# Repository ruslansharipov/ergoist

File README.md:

# Ergoist
Ergonomic fully split wireless keyboard

Main features: 
- ortholinear layout with 42 keys including 3 keys thumb cluster (just like on corne)
- all keys are 1u to make it easier to find keycaps
- pcb has big cutaway for battery, that can fit 35x30 lipo battery (should fit lipo 503035 500mA)
- designed to be used with Seeduino Xiao
- wireless only. Wired version will be supported it in future
- no screen integration (yet?)
- power switch (longer battery life, no accidental presses during transportation)
- works with ZMK, latest config can be found [here](https://github.com/ruslansharipov/ergoist-zmk-config)
- reversible PCB makes it cheaper in production (usually you can't order less than 5 pieces, so having 5 of those will make you able to assemble 2.5 keyboards)

Status:
- ~~pcb v0.1 in production~~ received, assembled, tested
- case **re**design

Latest images:

TODO
- update case design
- pcb cleanup
- partlist
- wired version
- screen integration
- touch sensor integration

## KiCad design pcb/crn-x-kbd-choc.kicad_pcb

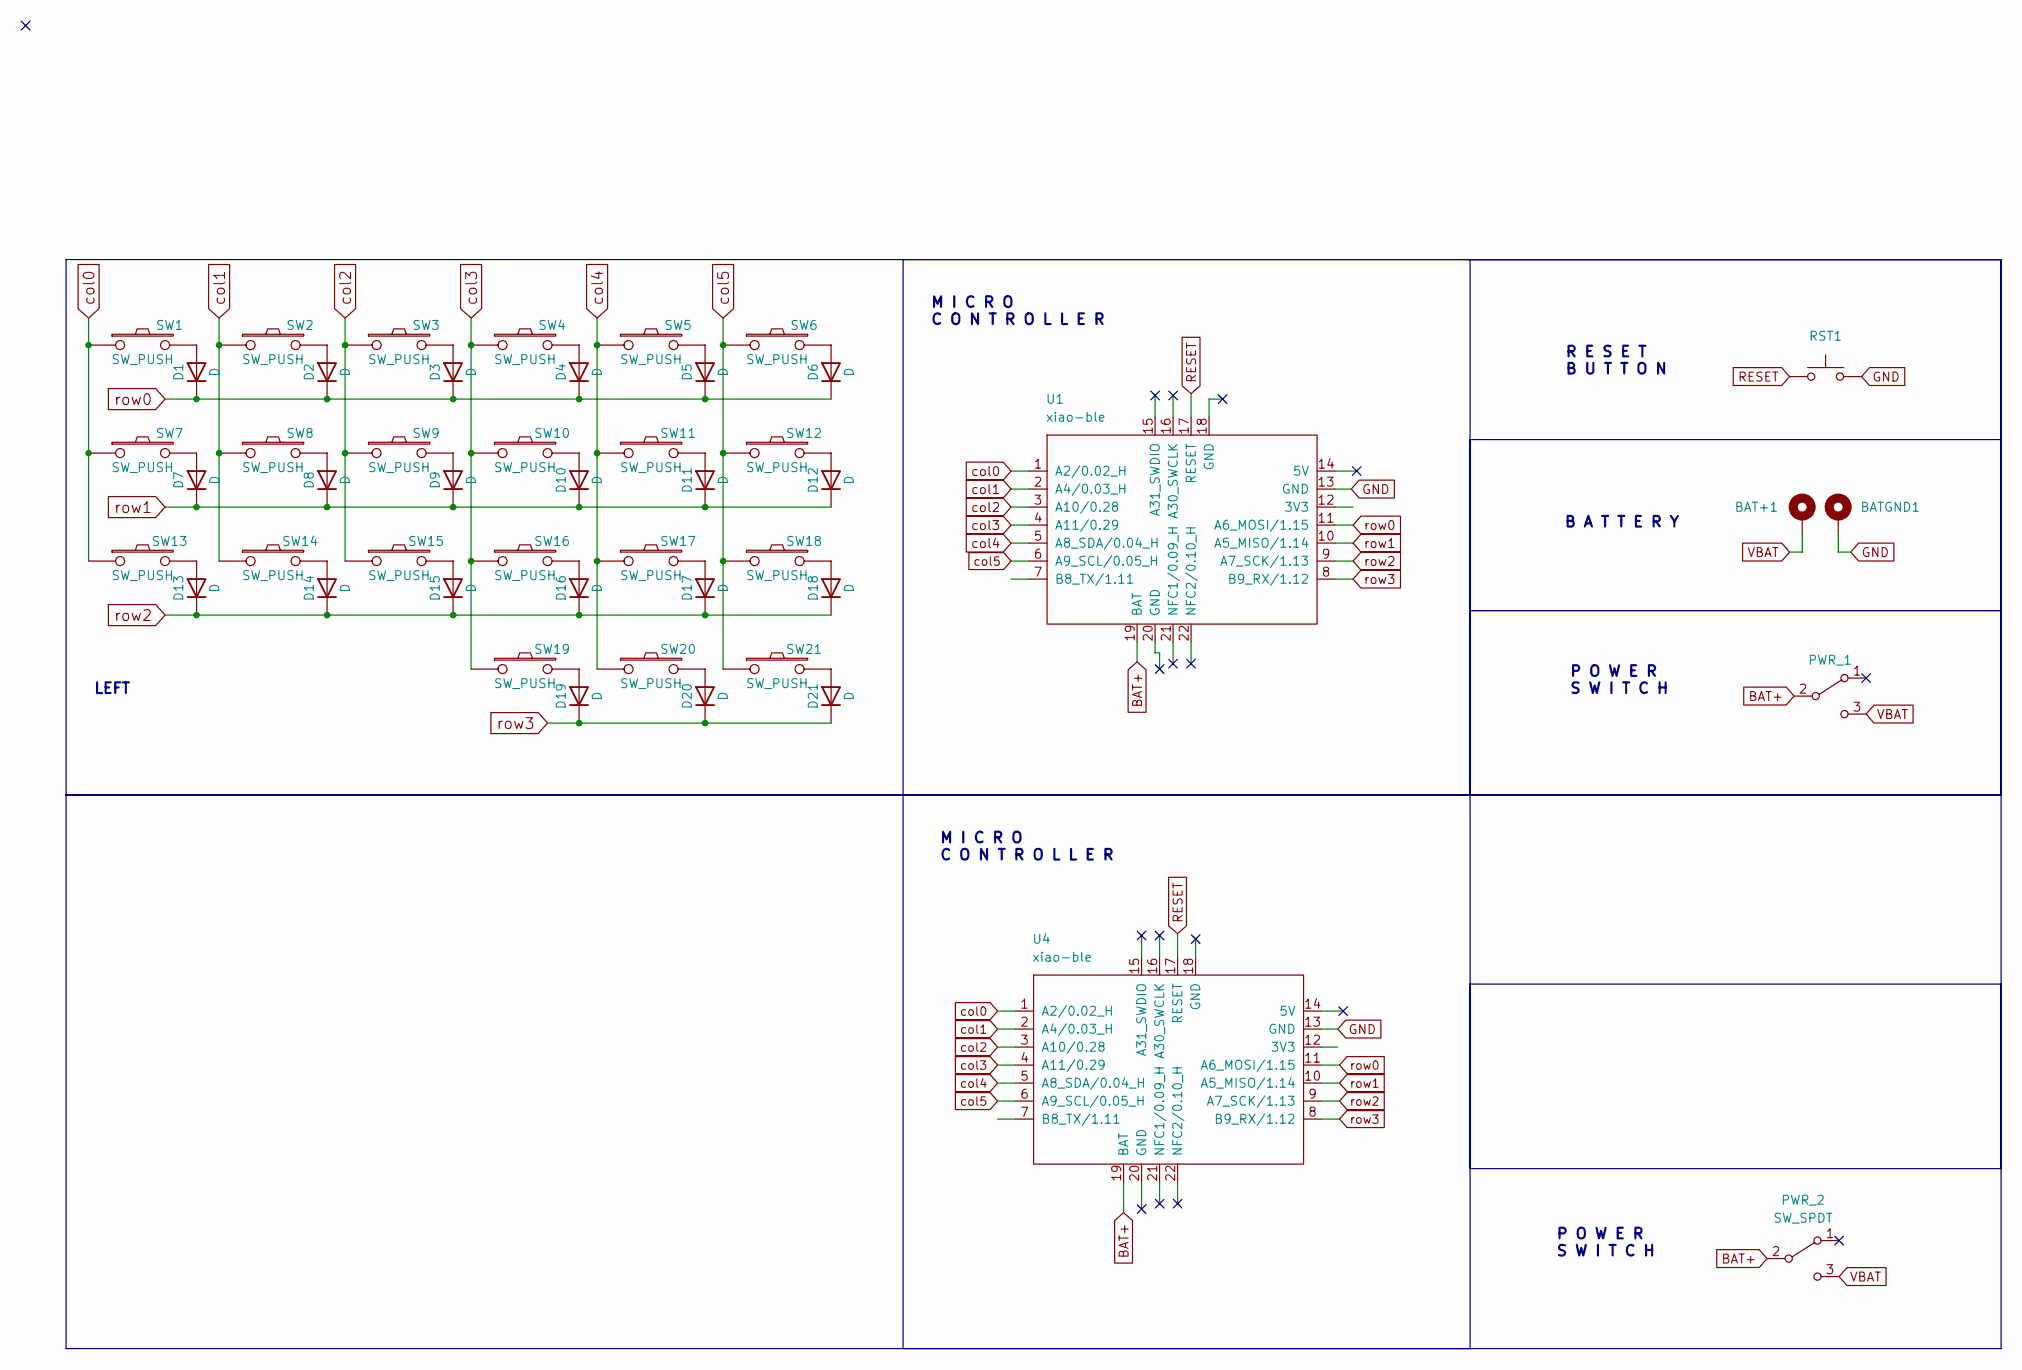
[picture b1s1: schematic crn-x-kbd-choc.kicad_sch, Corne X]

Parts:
BAT+1: +; BatteryPad
BATGND1: -; BatteryPad
D1, D2, D3, D4, D5, D6, D7, D8, D9, D10, D11, D12, D13, D14, D15, D16, D17, D18, D19, D20, D21: D; D3_TH_reversible
PWR_1, PWR_2: SW_SPDT; MSK12C02
RST1: SW_Push; SKHLLCA010_reversible
SW1, SW2, SW3, SW4, SW5, SW6, SW7, SW8, SW9, SW10, SW11, SW12, SW13, SW14, SW15, SW16, SW17, SW18, SW19, SW20, SW21: SW_PUSH; keyswitch_chock12_hotswap_1u_reversible
U1, U4: xiao-ble; xiao-ble-smd-cutout-one-side

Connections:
BAT+: PWR_1.2 (B), PWR_2.2 (B), U1.19 (BAT), U4.19 (BAT)
GND: BATGND1.1, RST1.2, U1.13 (GND), U4.13 (GND)
unnamed: D1.2 (A), SW1.2
unnamed: D2.2 (A), SW2.2
unnamed: D3.2 (A), SW3.2
unnamed: D4.2 (A), SW4.2
unnamed: D5.2 (A), SW5.2
unnamed: D6.2 (A), SW6.2
unnamed: D7.2 (A), SW7.2
unnamed: D8.2 (A), SW8.2
unnamed: D9.2 (A), SW9.2
unnamed: D10.2 (A), SW10.2
unnamed: D11.2 (A), SW11.2
unnamed: D12.2 (A), SW12.2
unnamed: D13.2 (A), SW13.2
unnamed: D14.2 (A), SW14.2
unnamed: D15.2 (A), SW15.2
unnamed: D16.2 (A), SW16.2
unnamed: D17.2 (A), SW17.2
unnamed: D18.2 (A), SW18.2
unnamed: D19.2 (A), SW19.2
unnamed: D20.2 (A), SW20.2
unnamed: D21.2 (A), SW21.2
RESET: RST1.1, U1.17 (RESET), U4.17 (RESET)
VBAT: BAT+1.1, PWR_1.3 (C), PWR_2.3 (C)
col0: SW1.1, SW7.1, SW13.1, U1.1 (A2/0.02_H), U4.1 (A2/0.02_H)
col1: SW2.1, SW8.1, SW14.1, U1.2 (A4/0.03_H), U4.2 (A4/0.03_H)
col2: SW3.1, SW9.1, SW15.1, U1.3 (A10/0.28), U4.3 (A10/0.28)
col3: SW4.1, SW10.1, SW16.1, SW19.1, U1.4 (A11/0.29), U4.4 (A11/0.29)
col4: SW5.1, SW11.1, SW17.1, SW20.1, U1.5 (A8_SDA/0.04_H), U4.5 (A8_SDA/0.04_H)
col5: SW6.1, SW12.1, SW18.1, SW21.1, U1.6 (A9_SCL/0.05_H), U4.6 (A9_SCL/0.05_H)
row0: D1.1 (K), D2.1 (K), D3.1 (K), D4.1 (K), D5.1 (K), D6.1 (K), U1.11 (A6_MOSI/1.15), U4.11 (A6_MOSI/1.15)
row1: D7.1 (K), D8.1 (K), D9.1 (K), D10.1 (K), D11.1 (K), D12.1 (K), U1.10 (A5_MISO/1.14), U4.10 (A5_MISO/1.14)
row2: D13.1 (K), D14.1 (K), D15.1 (K), D16.1 (K), D17.1 (K), D18.1 (K), U1.9 (A7_SCK/1.13), U4.9 (A7_SCK/1.13)
row3: D19.1 (K), D20.1 (K), D21.1 (K), U1.8 (B9_RX/1.12), U4.8 (B9_RX/1.12)

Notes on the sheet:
B A T T E R Y
R E S E T B U T T O N
P O W E R S W I T C H
LEFT
M I C R O C O N T R O L L E R

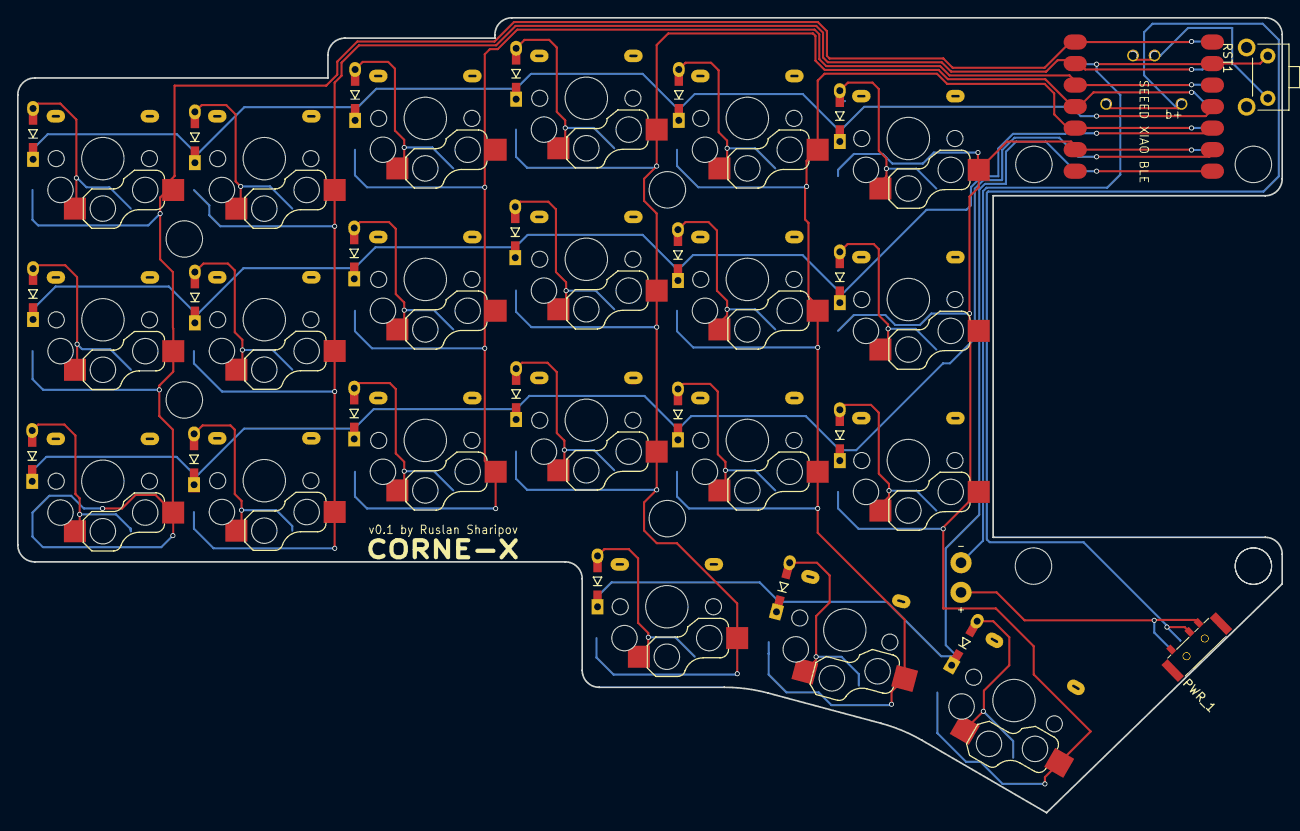
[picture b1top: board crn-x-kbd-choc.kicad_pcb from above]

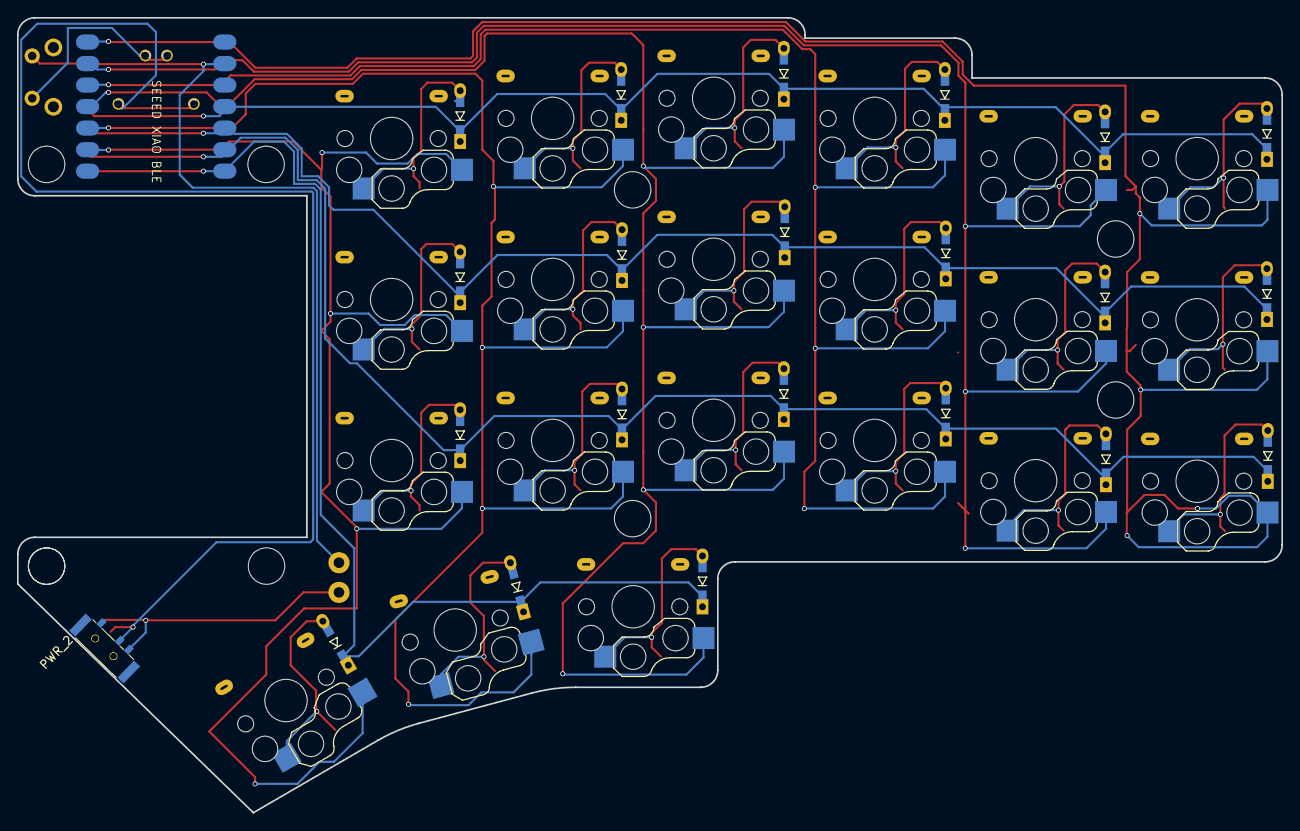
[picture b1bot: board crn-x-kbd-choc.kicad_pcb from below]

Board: 2 copper layers, 149.2 x 93.8 mm, 50 parts (23 on the bottom side), 35 nets.

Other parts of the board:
Ref**: Val**; M2_HOLE_v2

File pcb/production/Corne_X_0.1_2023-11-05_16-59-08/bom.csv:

Designator,Footprint,Quantity,Value,LCSC Part #
"_8, _7, _6, _5, _4, _3, _2, ",,8,,
BAT+1,BatteryPad,1,+,
BATGND1,BatteryPad,1,-,
"D1, D10, D11, D12, D13, D14, D15, D16, D17, D18, D19, D2, D20, D21, D3, D4, D5, D6, D7, D8, D9",D3_TH_reversible,21,D,
"PWR_1, PWR_2",MSK12C02,2,SW_SPDT,
RST1,SKHLLCA010_reversible,1,SW_Push,
"SW1, SW10, SW11, SW12, SW13, SW14, SW15, SW16, SW17, SW18, SW19, SW2, SW20, SW21, SW3, SW4, SW5, SW6, SW7, SW8, SW9",keyswitch_chock12_hotswap_1u_reversible,21,SW_PUSH,
"U1, U4",xiao-ble-smd-cutout-one-side,2,xiao-ble,

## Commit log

2023-11-06 version0_1
2023-12-05 other
2023-12-09 new_assets
2024-01-14 rename
